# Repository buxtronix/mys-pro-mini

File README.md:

# Mysensors low-power all-in-one node

This is an all-in-one node for Mysensors, with the following features designed:

 * Almost pin-for-pin compatible dropin for an Arduino Pro Mini
 * Low-power design for months of runtime on a CR2032
 * Built-in pads for an SMD NRF24L01 radio module, connected per [Mysensors standard](https://www.mysensors.org/build/connect_radio)
 * On-board SHT30 temperature and humidity sensor
 * On-board ATSHA204A crypto chip
 * Built in pads to mount a CR2032 coin cell holder
 * Ready to be sent to a fab-house such as [JLCPCB](https://jlcpcb.com)

Compatibility differences between a regular Arduino Pro Mini are:

 * No voltage regulator or power led (allows low-power operation), 3.3v max on VCC/RAW
 * A4/A5/A6/A7 shifted slightly to fit standard protoboard spacing

# Requirements

You should install the [Mysensors Kicad libraries](https://github.com/mysensors-kicad)
as this contains the NRF24L01 symbol/footprint.

Most other components should be available in a standard Kicad installation.

Extract/download all files into a subdirectory of your Kicad projects directory.

# Board manufacturing

I chose the components specifically for manufacture by JLCPCB. Component
choices, values and footprints were based upon their [component availability](https://jlcpcb.com/parts)
as at May 2021. The SMD components already have LCSC part numbers added to their properties.

Follow [their instructions](https://support.jlcpcb.com/article/149-how-to-generate-gerber-and-drill-files-in-kicad) for creating the necessary files for fab.
Note that the orientation of polarised components may differ from what you think,
but JLCPCB will confirm.

The radio is not provided by JLCPCB, however it's available from many places
such as Ebay, Banggood, Amazon, etc. Be sure to get the SMD version.

# Bootloader/firmware

A standard Arduino bootloader should be flashed, then you can upload any Arduino/Mysensors
projects to the board.

Note that your programmer needs to use 3.3v not 5v as the radio is only 3.3v tolerant
on VCC. If your programmer is only 5v, you will need to upload the firmware before
soldering on the radio board.
Alternatively, break JP4 during programming to disconnect the radio VCC. All other
components are 5v tolerant.

# Copyright

Available under the GPLv3.

Copyright 2021, Ben Buxton.

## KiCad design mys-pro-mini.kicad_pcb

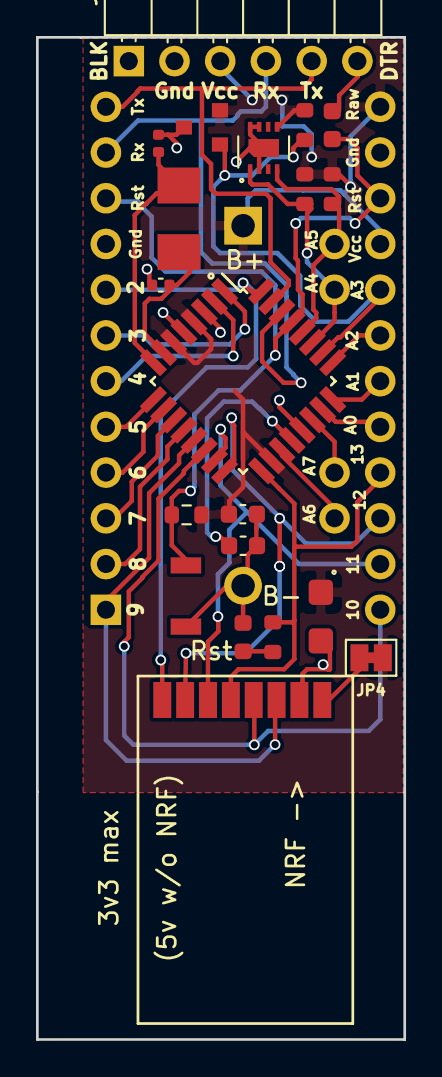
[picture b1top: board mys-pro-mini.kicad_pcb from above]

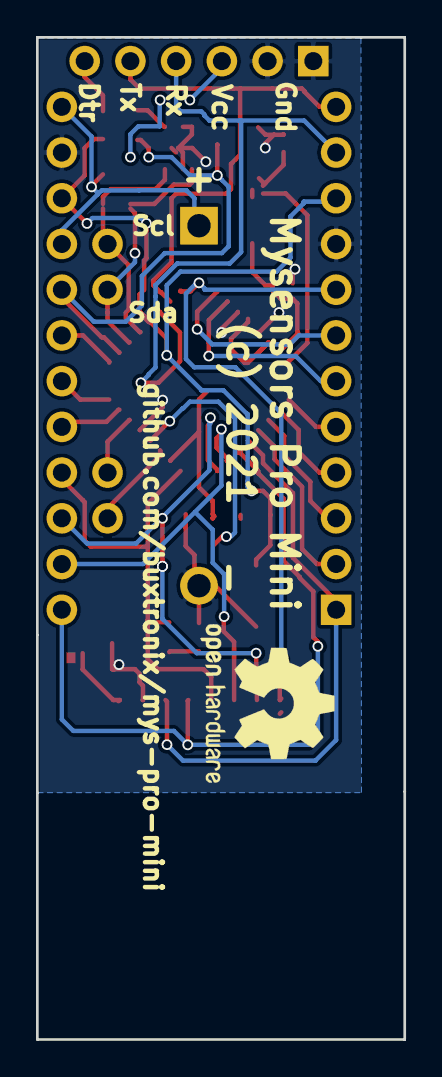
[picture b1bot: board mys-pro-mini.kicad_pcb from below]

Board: 2 copper layers, 20.4 x 55.7 mm, 25 parts (4 on the bottom side), 31 nets.

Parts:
BT1: Battery_Cell; BatteryHolder_ComfortableElectronic_CH273-2450_1x2450
C1, C2, C3: 0.1uF; C_0603_1608Metric
C4, C5: C; C_0402_1005Metric
C6: 10uF; CP_EIA-3216-18_Kemet-A
D3: Green; LED_0603_1608Metric
JP1: CONN_01X06; PinHeader_1x06_P2.54mm_Horizontal
JP2, JP3: CONN_01X02; PinHeader_1x02_P2.54mm_Vertical
JP4: SolderJumper_2_Bridged; SolderJumper-2_P1.3mm_Bridged_Pad1.0x1.5mm
JP6, JP7: CONN_01X12; PinHeader_1x12_P2.54mm_Vertical
R1, R3, R4: 4k7; R_0603_1608Metric
R2: 10k; R_0603_1608Metric
R6: 330; R_0603_1608Metric
S1: Reset; SW_SPST_B3U-1000P
U1: ATMEGA328-A; TQFP-32_7x7mm_P0.8mm
U2: NRF24L01; NRF24L01-SMD
U3: ATSHA204A; SOT-23
U4: SHT30-DIS; Sensirion_DFN-8-1EP_2.5x2.5mm_P0.5mm_EP1.1x1.7mm
Y1: Crystal_GND24; Crystal_SMD_5032-2Pin_5.0x3.2mm

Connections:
A0: JP6.8, U1.23
A1: JP6.7, U1.24
A2: JP6.6, U1.25
A3: JP6.5, R4.2, U1.26, U3.1
A4: JP2.1, R1.2, U1.27, U4.1
A5: JP2.2, R3.2, U1.28, U4.4
A6: JP3.1, U1.19
A7: JP3.2, U1.22
D2: JP7.8, U1.32, U2.8
D3: JP7.7, U1.1
D4: JP7.6, U1.2
D5: JP7.5, U1.9
D6: JP7.4, U1.10
D7: JP7.3, U1.11
D8: JP7.2, U1.12
D9: JP7.1, U1.13, U2.3
D10: JP6.12, U1.14, U2.4
DTR: C2.1, JP1.6
GND: BT1.2, C1.2, C3.2, C4.1, C5.1, C6.2, D3.1, JP1.1, JP1.2, JP6.2, JP7.9, S1.1, U1.3, U1.5, U1.21, U2.1, U3.3, U4.2, U4.7, U4.8, U4.9
MISO: JP6.10, U1.16, U2.7
MOSI: JP6.11, U1.15, U2.6
unnamed: C1.1, U1.20
unnamed: C4.2, U1.7, Y1.1
unnamed: C5.2, U1.8, Y1.2
unnamed: D3.2, R6.1
unnamed: JP4.2, U2.2
RESET: C2.2, JP6.3, JP7.10, R2.2, S1.2, U1.29
RXI: JP1.4, JP7.11, U1.30
SCK: JP6.9, R6.2, U1.17, U2.5
TXO: JP1.5, JP7.12, U1.31
VCC: BT1.1, C3.1, C6.1, JP1.3, JP4.1, JP6.1, JP6.4, R1.1, R2.1, R3.1, R4.1, U1.4, U1.6, U1.18, U3.2, U4.5

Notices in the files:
mys-pro-mini.kicad_pcb:
(c) 2021
